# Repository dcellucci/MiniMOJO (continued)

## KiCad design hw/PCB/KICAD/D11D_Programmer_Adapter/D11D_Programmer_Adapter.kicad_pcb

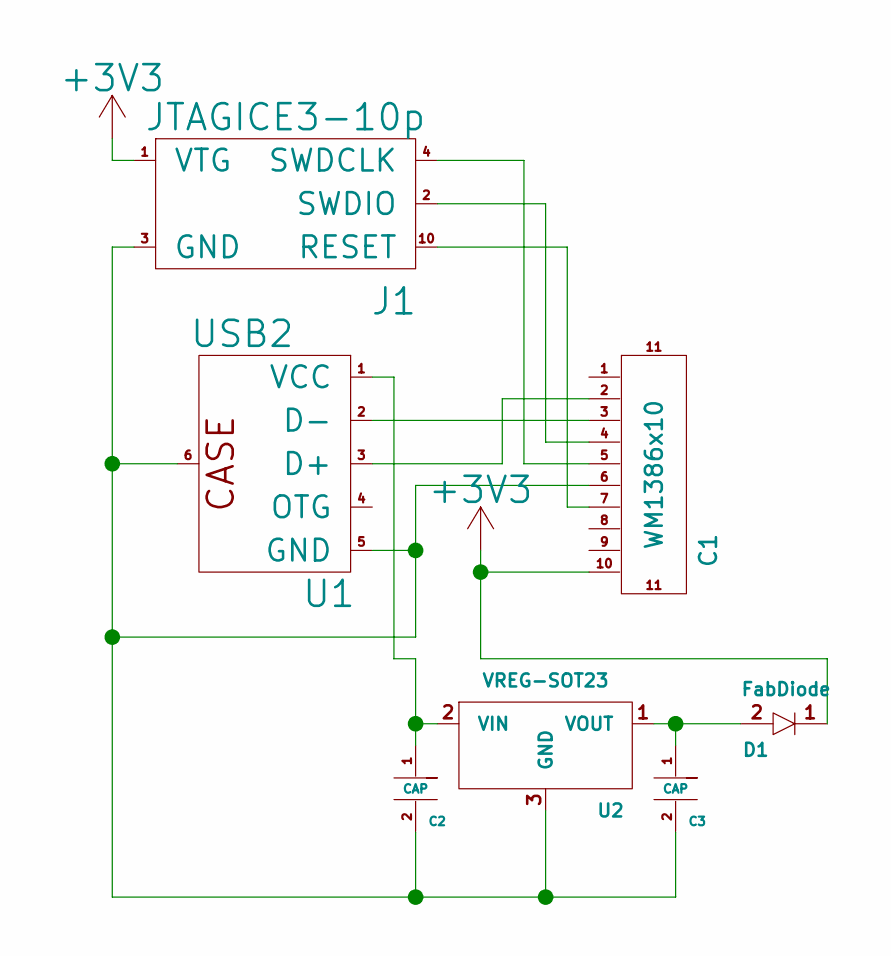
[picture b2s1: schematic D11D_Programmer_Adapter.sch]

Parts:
C1: WM1386x10; SMD-Header-5x2
C2, C3: CAP; CAP_1206_FAB
D1: FabDiode; LED_1206_FAB
J1: JTAGICE3-10p
U1: USB2; USBMINIB2.0
U2: VREG-SOT23; SOT-23

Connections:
+3V3: C1.10, D1.1, J1.1 (VTG)
unnamed: C1.2, U1.3 (D+)
unnamed: C1.3, U1.2 (D-)
unnamed: C1.4, J1.2 (SWDIO)
unnamed: C1.5, J1.4 (SWDCLK)
unnamed: C1.6, C2.2, C3.2, J1.3 (GND), U1.5 (GND), U1.6, U2.3 (GND)
unnamed: C1.7, J1.10 (RESET)
unnamed: C2.1, U1.1 (VCC), U2.2 (VIN)
unnamed: C3.1, D1.2, U2.1 (VOUT)

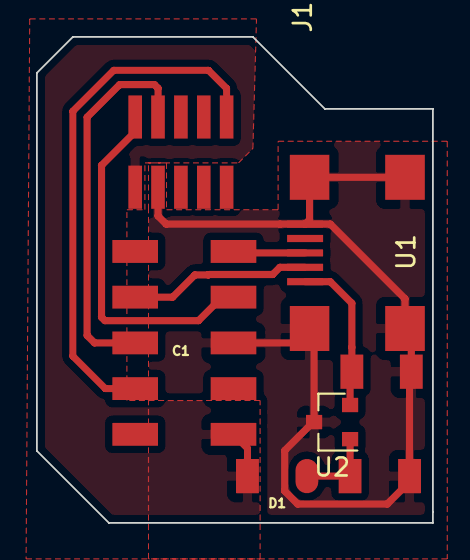
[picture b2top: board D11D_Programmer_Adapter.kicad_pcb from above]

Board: 2 copper layers, 22.0 x 27.0 mm, 7 parts (0 on the bottom side), 9 nets.

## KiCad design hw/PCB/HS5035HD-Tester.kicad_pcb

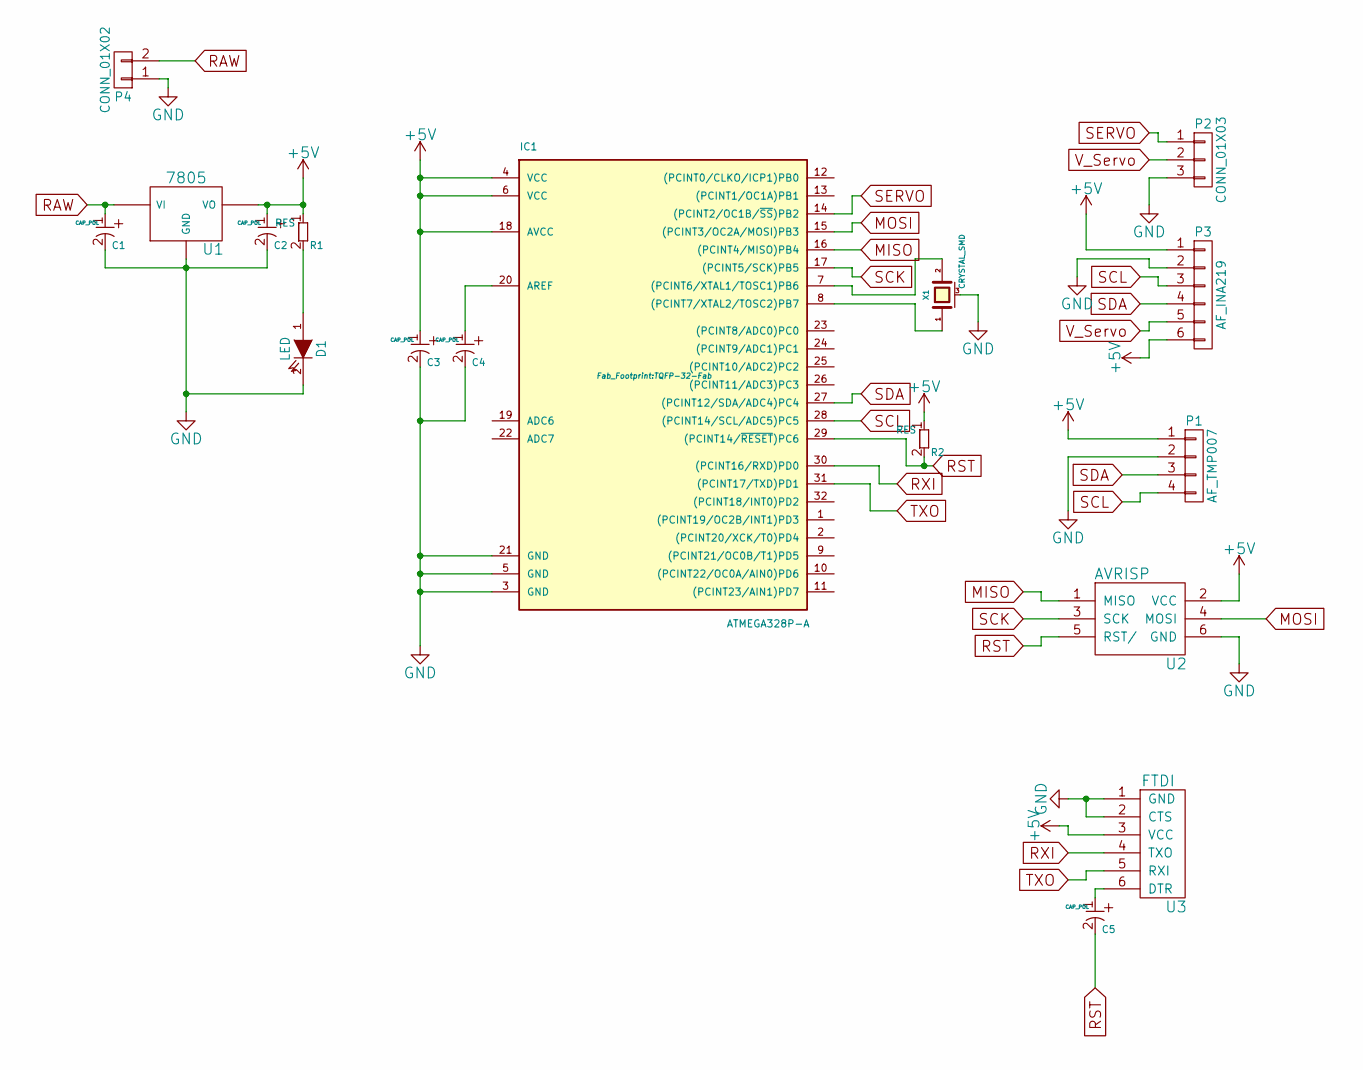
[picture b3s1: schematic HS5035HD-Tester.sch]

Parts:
C1, C2, C3, C4, C5: CAP_POL; CAP_1206_FAB
D1: LED; CAP_1206_FAB
IC1: ATMEGA328P-A; TQFP-32-Fab
P1: AF_TMP007; SMD_RA_1x04_No_Holes
P2: CONN_01X03; SMD_RA_1x03_No_Holes
P3: AF_INA219; SMD_RA_1x06_No_Holes
P4: CONN_01X02; TerminalBlock_Pheonix_MKDS1.5-2pol
R1, R2: RES; CAP_1206_FAB
U1: 7805; SOT-223
U2: AVRISP; SMD_2x03
U3: FTDI; SMD_RA_1x06_No_Holes
X1: CRYSTAL_SMD; RESONATOR

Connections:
+5V: C2.1, C3.1, IC1.4 (VCC), IC1.6 (VCC), IC1.18 (AVCC), P1.1, P3.1, P3.6, R1.1, R2.1, U1.2 (VO), U2.2 (VCC), U3.3 (VCC)
GND: C1.2, C2.2, C3.2, C4.2, D1.2 (K), IC1.3 (GND), IC1.5 (GND), IC1.21 (GND), P1.2, P2.3, P3.2, P4.1, U1.1 (GND), U2.6 (GND), U3.1 (GND), U3.2 (CTS), X1.3 (case)
MISO: IC1.16 ((PCINT4/MISO)PB4), U2.1 (MISO)
MOSI: IC1.15 ((PCINT3/OC2A/MOSI)PB3), U2.4 (MOSI)
unnamed: C4.1, IC1.20 (AREF)
unnamed: C5.1, U3.6 (DTR)
unnamed: D1.1 (A), R1.2
unnamed: IC1.7 ((PCINT6/XTAL1/TOSC1)PB6), X1.2
unnamed: IC1.8 ((PCINT7/XTAL2/TOSC2)PB7), X1.1
RAW: C1.1, P4.2, U1.3 (VI)
RST: C5.2, IC1.29 ((PCINT14/~RESET~)PC6), R2.2, U2.5 (RST/)
RXI: IC1.30 ((PCINT16/RXD)PD0), U3.4 (TXO)
SCK: IC1.17 ((PCINT5/SCK)PB5), U2.3 (SCK)
SCL: IC1.28 ((PCINT14/SCL/ADC5)PC5), P1.4, P3.3
SDA: IC1.27 ((PCINT12/SDA/ADC4)PC4), P1.3, P3.4
SERVO: IC1.14 ((PCINT2/OC1B/~SS~)PB2), P2.1
TXO: IC1.31 ((PCINT17/TXD)PD1), U3.5 (RXI)
V_Servo: P2.2, P3.5

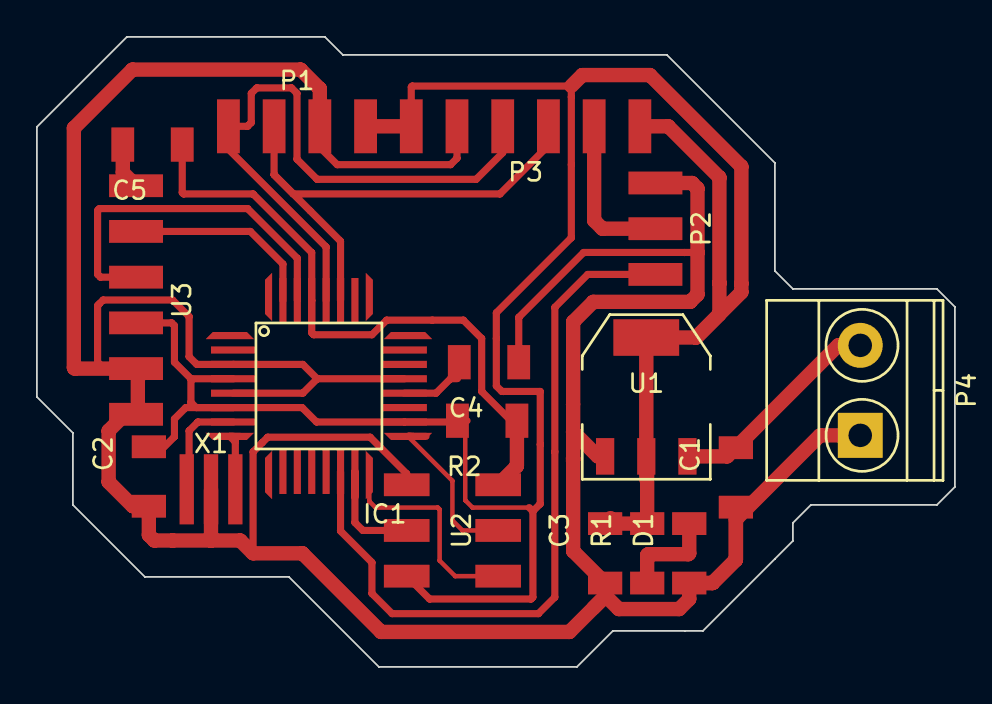
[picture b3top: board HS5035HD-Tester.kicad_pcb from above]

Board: 2 copper layers, 51.0 x 35.0 mm, 17 parts (0 on the bottom side), 18 nets.

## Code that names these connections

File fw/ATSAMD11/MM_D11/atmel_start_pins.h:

/*
 * Code generated from Atmel Start.
 *
 * This file will be overwritten when reconfiguring your Atmel Start project.
 * Please copy examples or other code you want to keep to a separate file
 * to avoid losing it when reconfiguring.
 */
#ifndef ATMEL_START_PINS_H_INCLUDED
#define ATMEL_START_PINS_H_INCLUDED

#include <hal_gpio.h>

#define PA04 GPIO(GPIO_PORTA, 4)
#define PA05 GPIO(GPIO_PORTA, 5)
#define PA06 GPIO(GPIO_PORTA, 6)
#define PA14 GPIO(GPIO_PORTA, 14)
#define PA15 GPIO(GPIO_PORTA, 15)
#define PA22 GPIO(GPIO_PORTA, 22)
#define PA23 GPIO(GPIO_PORTA, 23)

#endif // ATMEL_START_PINS_H_INCLUDED

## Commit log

2016-08-25 Added Gear Generation notes
2016-08-26 Added CAD files of MOJO
2016-08-29 updated CAD, added Eagle Boards (ATSAM and ATMEGA)
2016-08-29 Added TPS61089 library
2016-08-30 Made TPS61089 mods
2016-09-02 added TPS61089 w/ Tiny841
2016-09-02 Added finished 841 schematic
2016-09-03 Added new MM arms
2016-09-03 added full 841 board
2016-09-07 added new arms, control code
2016-09-08 making changes
2016-09-23 too long since commiting...
2016-09-23 removed 3dm's (because they're huge)
2016-09-23 removed more 3dms
2016-09-23 added descriptive sw tutorial (start)
2016-09-23 smaller images
2016-09-23 changed image size 2
2016-09-24 Added spline pattern
2016-09-24 updated hub drawing
2016-11-15 post 0g
2016-11-15 Adding CC (computer control) code
2016-11-15 Added readme for computer controller
2016-11-15 improved readme for computer controller
2016-11-15 Added current reading output parsing
2016-11-15 cleaning
2016-11-16 ascii art
2016-11-16 Changed servo order to appease people
2016-11-20 Test Stand models
2016-11-21 Added Fab Modules UI
2016-11-30 Added custom modules
2017-02-09 Rev 3 MM boards and Migration to KICAD
2017-02-09 Added annotated platecad
2017-02-10 ATSAMD11_Core layout using KiCAD
2017-02-11 Added hex spacer, reorganized CAD modules
2017-02-11 Added board stack spacer
2017-02-13 Added ATSAMD11 AAtmel smart code
2017-02-16 Added stp files for updated MM components
2017-02-22 long time since commit
2017-02-22 new lib INA3221
2017-02-23 added include wire statement
2017-02-23 INA3221 refactor to class and format like dps310
2017-02-23 Added serial javascript files
2017-02-23 moved INA3221 to CSL-Part-Library
2017-02-27 Lots of changes- firmware, board rev, mods
2017-02-28 Added addendum to boards, modules for debug, comms description
2017-02-28 V1 Comms Spec
2017-02-28 more comms edits
2017-02-28 fixing github problems
2017-02-28 github debug
2017-02-28 line spacing...?
2017-02-28 that didn't work
2017-02-28 finally?
2017-03-02 Latency Test, firmware development
2017-03-02 working ingest of mojo json
2017-03-03 more firmware, a working websocket serial node
2017-03-03 cleanedup getMojoJsonData.js
2017-03-06 Added IK input information
2017-03-15 fixed connection; wasn't passing comm port to serial open()
2017-03-15 working WINDOWS websocket; tmp fix on malformed json possibly from irregular event call
2017-03-15 added DISPLAY2.js
2017-03-17 added working data_logger.js
2017-03-17 updated websocket for windows; working power mon and data logger
2017-03-18 working mojo plotting = MOJO_canvas_plotter
2017-03-20 ...I forgot to commit for a while
2017-03-20 Added firmware def
2017-03-20 added motor positions
2017-03-20 added servomotor value descriptions
2017-04-04 Adding latency tests + serial work
2017-04-06 Added mojo scheduler
2017-04-11 translated results from 0g test (day 2)
